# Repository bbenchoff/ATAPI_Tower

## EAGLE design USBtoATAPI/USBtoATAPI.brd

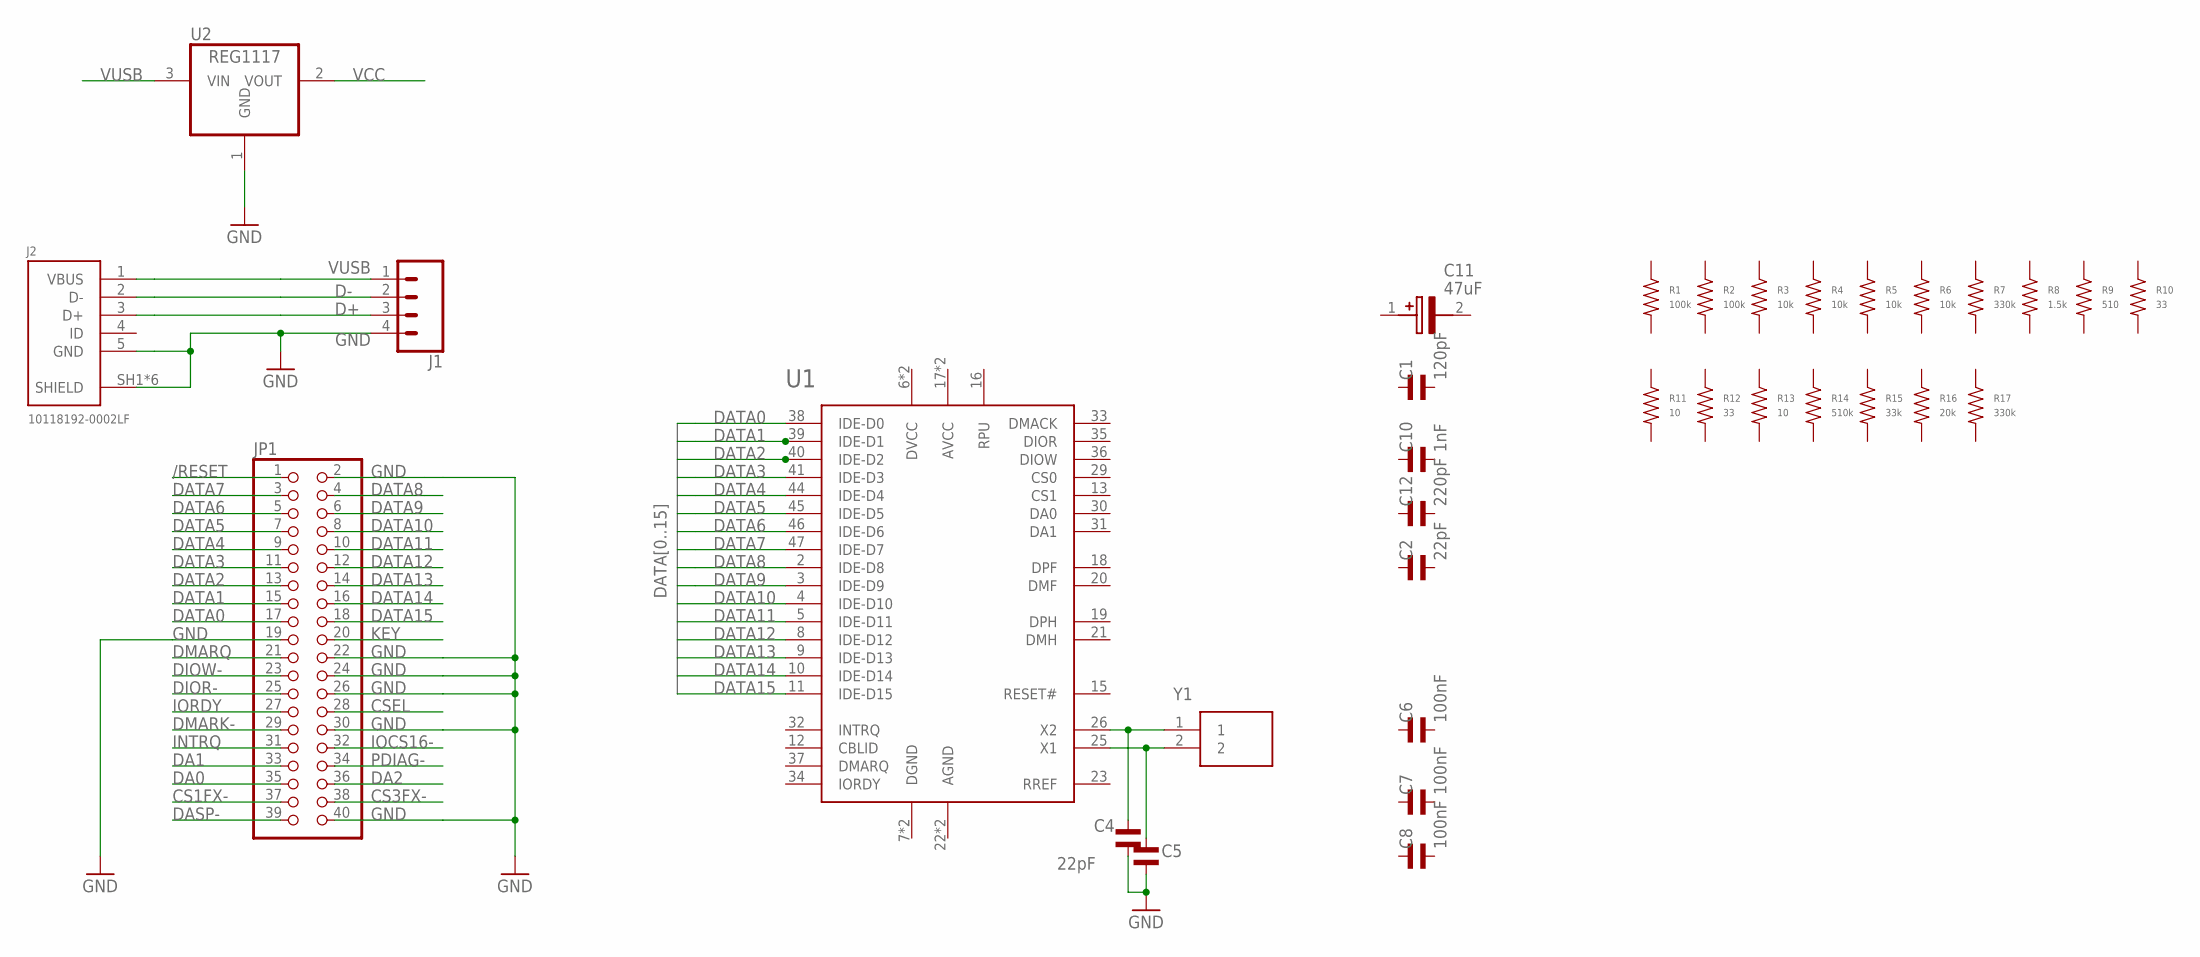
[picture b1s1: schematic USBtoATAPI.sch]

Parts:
C1: 120pF; C0805
C2, C4, C5: 22pF; C0805
C6, C7, C8: 100nF; C0805
C10: 1nF; C0805
C11: 47uF; CAPAE430X550N
C12: 220pF; C0805
J1: CONN_04JST-PTH-VERT; JST-4-PTH-VERT
J2: 10118192-0002LF
JP1: PINHD-2X20; 2X20
R1, R2: 100k; R0805
R3, R4, R5, R6: 10k; R0805
R7, R17: 330k; R0805
R8: 1.5k; R0805
R9: 510; R0805
R10, R12: 33; R0805
R11, R13: 10; R0805
R14: 510k; R0805
R15: 33k; R0805
R16: 20k; R0805
U1: GL811E; LQFP-48
U2: REG1117; SOT223
Y1: 445C33C12M00000

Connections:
/RESET: JP1.1
CS1FX-: JP1.37
CS3FX-: JP1.38
CSEL: JP1.28
D+: J1.3, J2.3 (D+)
D-: J1.2, J2.2 (D-)
DA0: JP1.35
DA1: JP1.33
DA2: JP1.36
DASP-: JP1.39
DATA0: JP1.17, U1.38 (IDE-D0), U1.39 (IDE-D1)
DATA1: JP1.15, U1.40 (IDE-D2)
DATA2: JP1.13
DATA3: JP1.11, U1.41 (IDE-D3)
DATA4: JP1.9, U1.44 (IDE-D4)
DATA5: JP1.7, U1.45 (IDE-D5)
DATA6: JP1.5, U1.46 (IDE-D6)
DATA7: JP1.3, U1.47 (IDE-D7)
DATA8: JP1.4, U1.2 (IDE-D8)
DATA9: JP1.6, U1.3 (IDE-D9)
DATA10: JP1.8, U1.4 (IDE-D10)
DATA11: JP1.10, U1.5 (IDE-D11)
DATA12: JP1.12, U1.8 (IDE-D12)
DATA13: JP1.14, U1.9 (IDE-D13)
DATA14: JP1.16, U1.10 (IDE-D14)
DATA15: JP1.18, U1.11 (IDE-D15)
DIOR-: JP1.25
DIOW-: JP1.23
DMARK-: JP1.29
DMARQ: JP1.21
GND: C4.P$2, C5.P$1, J1.4, J2.5 (GND), J2.SH1 (SHIELD), J2.SH2 (SHIELD), J2.SH3 (SHIELD), J2.SH4 (SHIELD), J2.SH5 (SHIELD), J2.SH6 (SHIELD), JP1.2, JP1.19, JP1.22, JP1.24, JP1.26, JP1.30, JP1.40, U2.1 (GND)
INTRQ: JP1.31
IOCS16-: JP1.32
IORDY: JP1.27
KEY: JP1.20
unnamed: C4.P$1, U1.26 (X2), Y1.1
unnamed: C5.P$2, U1.25 (X1), Y1.2
PDIAG-: JP1.34
VCC: U2.2 (VOUT)
VUSB: J1.1, J2.1 (VBUS), U2.3 (VIN)

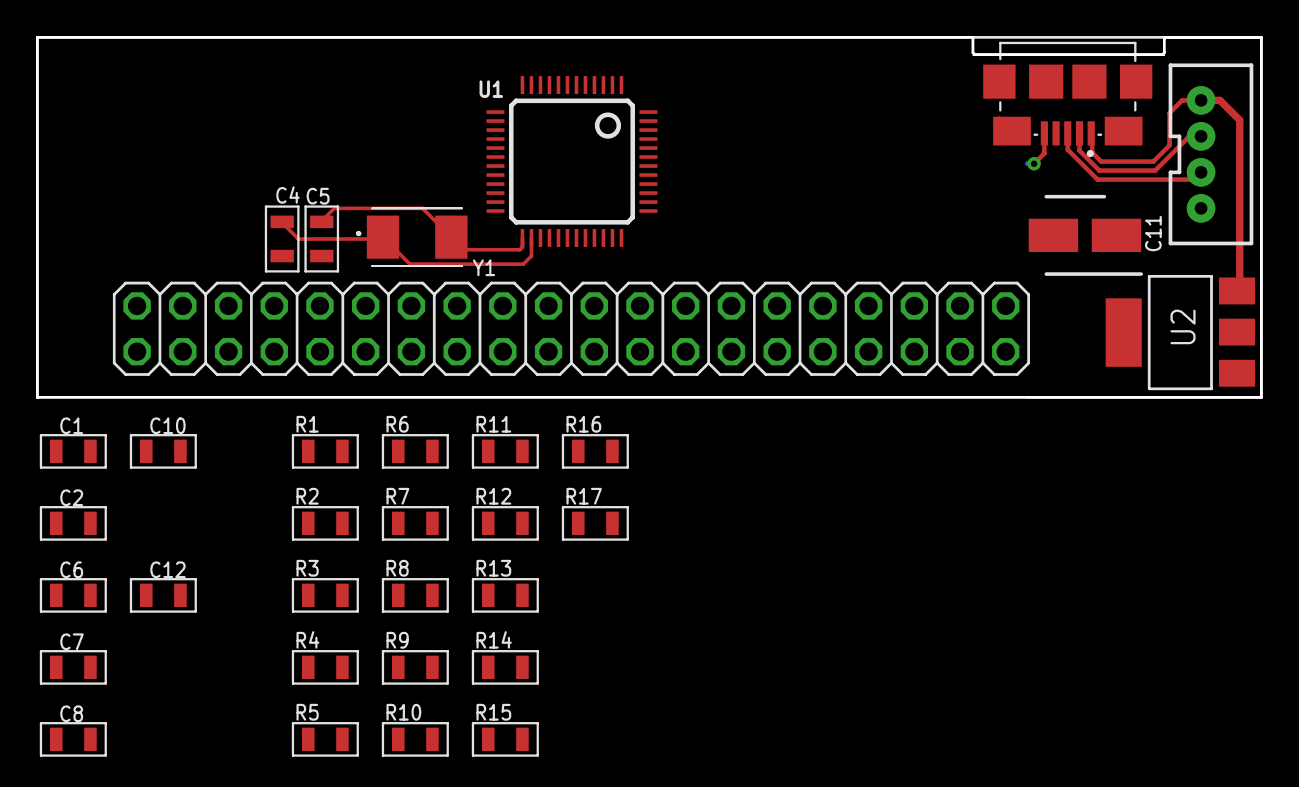
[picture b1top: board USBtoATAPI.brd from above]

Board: 2 copper layers, 68.0 x 20.0 mm, 33 parts (0 on the bottom side), 21 nets.

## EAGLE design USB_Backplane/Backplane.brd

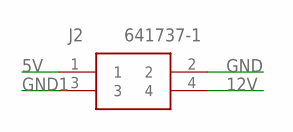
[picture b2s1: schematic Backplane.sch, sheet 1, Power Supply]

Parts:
J2: 641737-1

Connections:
5V: J2.1; also elsewhere on the board
12V: J2.4
GND: J2.2; also elsewhere on the board
GND1: J2.3

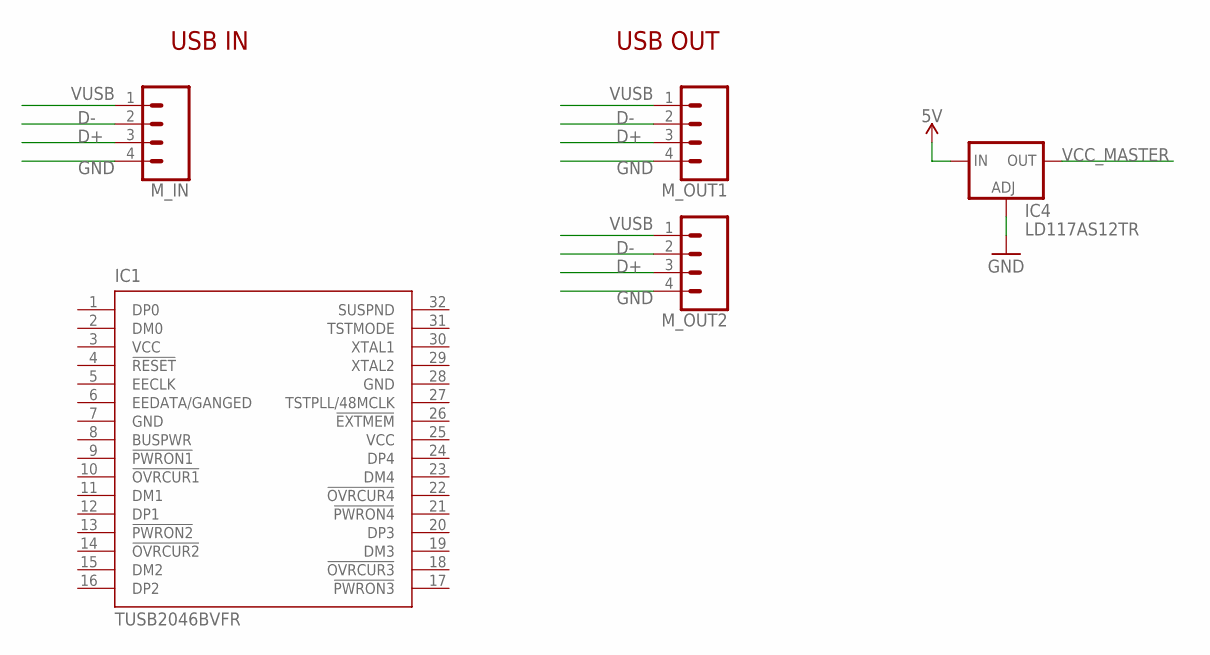
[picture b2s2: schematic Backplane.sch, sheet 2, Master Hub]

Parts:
IC1: TUSB2046BVFR; VF_S-PQFP-G32
IC4: LD117AS12TR; SOT223
M_IN: CONN_04JST-PTH-VERT; JST-4-PTH-VERT
M_OUT1, M_OUT2: CONN_04JST-PTH-VERT; JST-4-PTH-VERT

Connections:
5V: IC4.3 (IN); also elsewhere on the board
D+: M_IN.3, M_OUT1.3, M_OUT2.3
D-: M_IN.2, M_OUT1.2, M_OUT2.2
GND: IC1.7 (GND), IC1.28 (GND), IC4.1 (ADJ), M_IN.4, M_OUT1.4, M_OUT2.4; also elsewhere on the board
VCC: IC1.3 (VCC), IC1.25 (VCC)
VCC_MASTER: IC4.4 (OUT)
VUSB: M_IN.1, M_OUT1.1, M_OUT2.1

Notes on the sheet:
USB IN
USB OUT

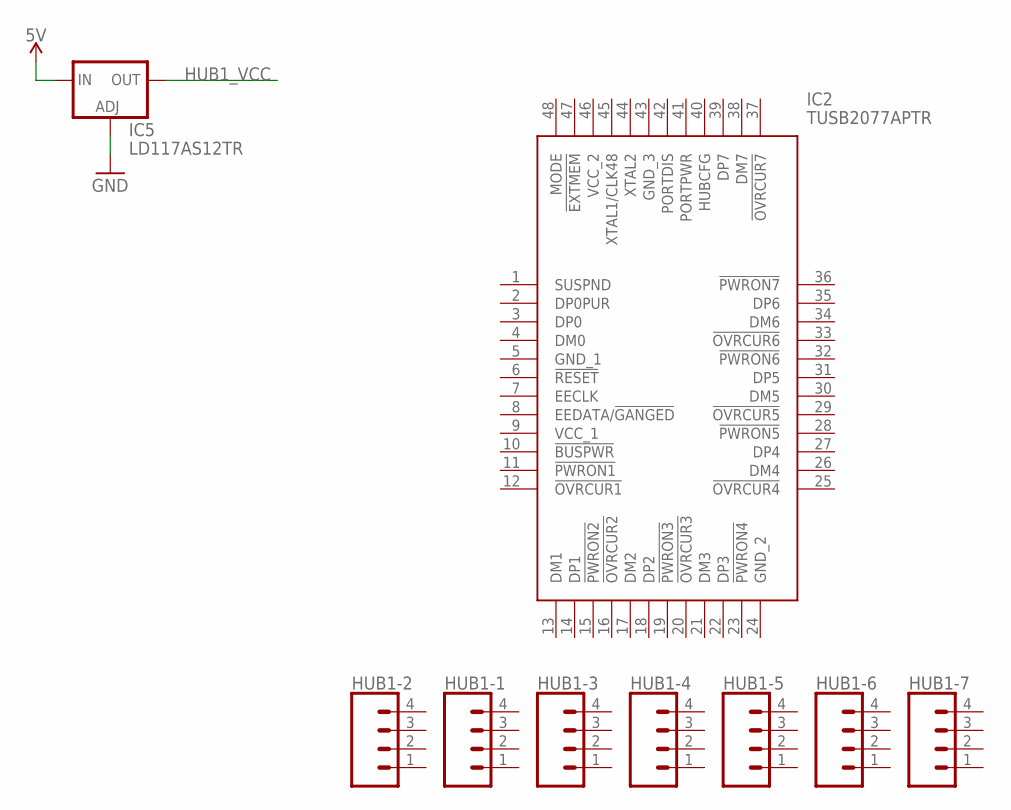
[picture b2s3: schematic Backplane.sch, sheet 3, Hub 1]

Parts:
HUB1-1, HUB1-2, HUB1-3, HUB1-4, HUB1-5, HUB1-6, HUB1-7: CONN_04JST-PTH-VERT; JST-4-PTH-VERT
IC2: TUSB2077APTR; QFP50P900X900X160-48N
IC5: LD117AS12TR; SOT223

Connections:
5V: IC5.3 (IN); also elsewhere on the board
GND: IC5.1 (ADJ); also elsewhere on the board
HUB1_VCC: IC5.4 (OUT)

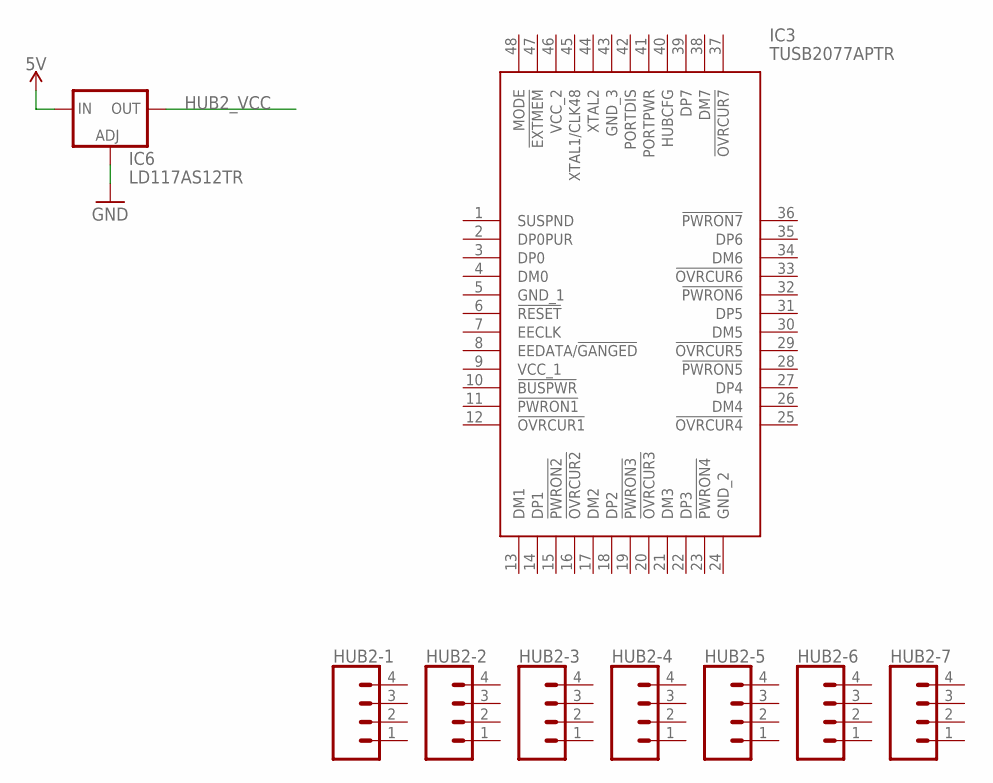
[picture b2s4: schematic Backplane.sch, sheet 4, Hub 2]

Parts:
HUB2-1, HUB2-2, HUB2-3, HUB2-4, HUB2-5, HUB2-6, HUB2-7: CONN_04JST-PTH-VERT; JST-4-PTH-VERT
IC3: TUSB2077APTR; QFP50P900X900X160-48N
IC6: LD117AS12TR; SOT223

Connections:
5V: IC6.3 (IN); also elsewhere on the board
GND: IC6.1 (ADJ); also elsewhere on the board
HUB2_VCC: IC6.4 (OUT)

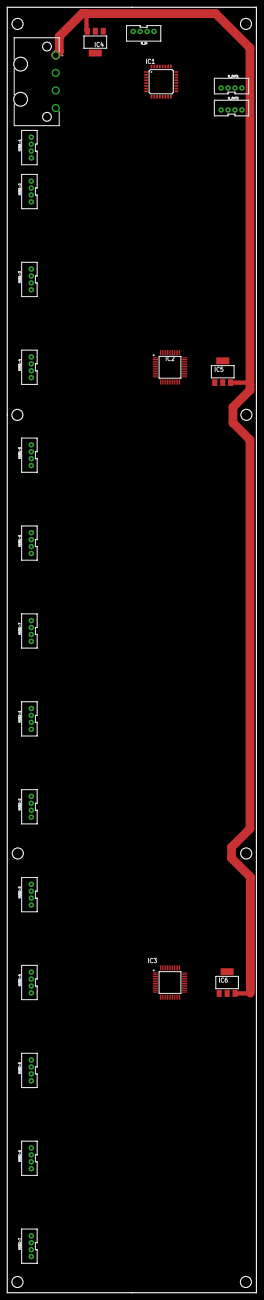
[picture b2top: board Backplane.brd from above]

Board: 2 copper layers, 72.0 x 371.5 mm, 24 parts (0 on the bottom side), 6 nets.

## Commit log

2019-08-18 Initial
2019-08-18 Slightly Modified
2019-08-19 Updated side top bottom
2019-08-19 Finished mechanical, added BOM
2019-08-20 Added backplane template
2019-08-21 Push illus
2019-08-21 fixed panels
2019-08-21 slight another fix
2019-08-22 Grouped everything
2019-08-22 I think it's done
2019-08-23 add art assets
2019-08-24 started electronics
2019-08-28 Created outside panel
2019-09-15 did PCB panel
2019-09-17 Fixed panel
2019-09-17 updated to 16-bay enclosure
2019-11-23 Down to 15-bay enclosure
    Changed everything to fit on a laser cutter, it will now be a 15-bay enclosure, with one bay at the top for electronics. This is great, because 14/2=7 and I can get 7-port USB hubs.
2019-11-25 fixed stuff
2020-08-10 did some stuff
2020-08-18 Started layout

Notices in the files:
parts and their libraries:
SparkFun-Connectors: Licensing: Creative Commons ShareAlike 4.0 International - https://creativecommons.org/licenses/by-sa/4.0
